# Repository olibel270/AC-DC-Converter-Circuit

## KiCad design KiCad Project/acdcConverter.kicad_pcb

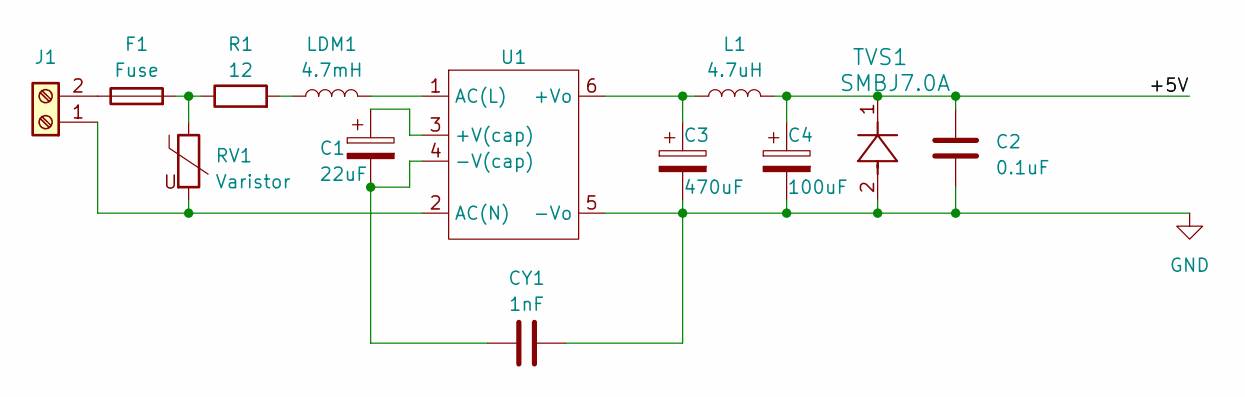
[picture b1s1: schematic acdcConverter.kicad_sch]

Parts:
C1: 22uF; CP_Radial_D12.5mm_P5.00mm
C2: 0.1uF; C_0805_2012Metric
C3: 470uF; CP_Radial_D8.0mm_P3.50mm
C4: 100uF; CP_Elec_6.3x7.7
CY1: 1nF; C_Disc_D8.0mm_W5.0mm_P7.50mm
F1: Fuse; FUSE_SS-5H-1A_EAT
J1: Screw_Terminal_01x02; TerminalBlock_Phoenix_MKDS-1,5-2_1x02_P5.00mm_Horizontal
L1: 4.7uH; L_Changjiang_FNR3021S
LDM1: 4.7mH; L_Radial_D7.8mm_P5.00mm_Fastron_07HCP
R1: 12; R_Axial_DIN0414_L11.9mm_D4.5mm_P15.24mm_Horizontal
RV1: Varistor; RV_Disc_D12mm_W3.9mm_P7.5mm
TVS1: SMBJ7.0A; SMBJSeries_LTF
U1: LS05-13B05R3

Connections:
/+5V: C2.1, C4.1, L1.2, TVS1.1
GND: C2.2, C3.2, C4.2, CY1.2, TVS1.2, U1.5 (-Vo)
unnamed: F1.2, R1.1, RV1.1
unnamed: J1.1, RV1.2, U1.2 (AC(N))
unnamed: F1.1, J1.2
unnamed: LDM1.1, R1.2
unnamed: C1.1, U1.3 (+V(cap))
unnamed: C3.1, L1.1, U1.6 (+Vo)
unnamed: C1.2, CY1.1, U1.4 (-V(cap))
unnamed: LDM1.2, U1.1 (AC(L))

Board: 2 copper layers, 13 parts (0 on the bottom side), 10 nets, no tracks yet.

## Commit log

2023-12-01 Made two different folders
2025-01-30 Save For Backup Day
